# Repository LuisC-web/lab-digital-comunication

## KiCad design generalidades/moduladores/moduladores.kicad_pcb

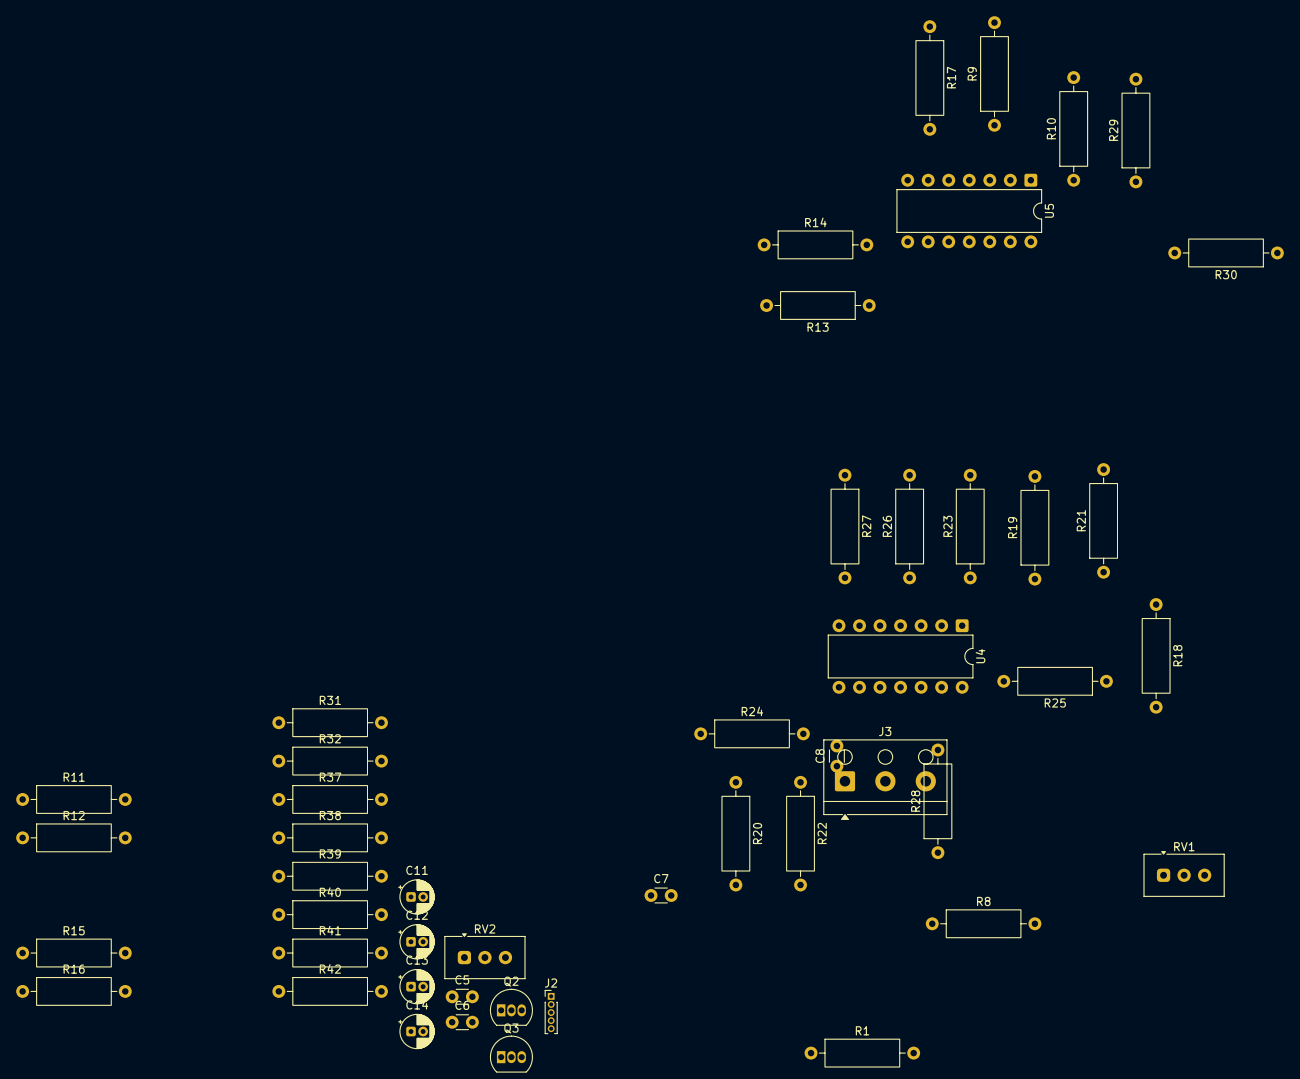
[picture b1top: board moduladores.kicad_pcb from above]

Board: 2 copper layers, 48 parts (0 on the bottom side), 31 nets, no tracks yet.

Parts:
C5, C6, C7, C8: 100nF; C_Disc_D3.0mm_W1.6mm_P2.50mm
C11, C13: 0.1uF; CP_Radial_D4.0mm_P1.50mm
C12, C14: 10uF; CP_Radial_D4.0mm_P1.50mm
J2: Entradas-salidas; PinHeader_1x05_P1.00mm_Vertical
J3: Fuente; TerminalBlock_RND_205-00002_1x03_P5.00mm_Horizontal
Q2, Q3: 2N3904; TO-92_Inline
R1, R8, R18, R19: 10K; R_Axial_DIN0309_L9.0mm_D3.2mm_P12.70mm_Horizontal
R9, R26: 6.8k; R_Axial_DIN0309_L9.0mm_D3.2mm_P12.70mm_Horizontal
R10, R11, R15, R21, R22, R23: 51; R_Axial_DIN0309_L9.0mm_D3.2mm_P12.70mm_Horizontal
R12, R13, R14, R20, R24, R25, R29, R32: 1k; R_Axial_DIN0309_L9.0mm_D3.2mm_P12.70mm_Horizontal
R16, R17, R27, R28: 3.9k; R_Axial_DIN0309_L9.0mm_D3.2mm_P12.70mm_Horizontal
R30, R31: 100k; R_Axial_DIN0309_L9.0mm_D3.2mm_P12.70mm_Horizontal
R37, R38, R39, R40, R41, R42: 220k; R_Axial_DIN0309_L9.0mm_D3.2mm_P12.70mm_Horizontal
RV1, RV2: 50k; Potentiometer_Vishay_T93YA_Vertical
U4, U5: MC1496; DIP-14_W7.62mm

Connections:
+12V: J3.1, Q2.3 (C), Q3.3 (C), R14.1, R16.1, R17.1, R24.1, R27.1, R28.1, R37.1, R40.1
-12V: J3.3, RV1.2, RV2.2, U4.14 (Vee), U5.14 (Vee)
Bcos(wt): C5.1, C12.2
Bsen(wt): C7.1, C14.2
GND: C6.1, C8.1, J3.2, R9.2, R10.2, R11.2, R13.2, R20.2, R21.2, R23.2, R26.2, R29.2, R32.2, R38.2, R39.2, R41.2, R42.2
unnamed: C5.2, R15.2, U5.10
unnamed: C6.2, R13.1, R14.2, R15.1, U5.8
unnamed: C7.2, R22.2, U4.10
unnamed: C8.2, R20.1, R22.1, R24.2, U4.8
unnamed: C13.2, Q2.2 (B), R40.2, R41.1
unnamed: C14.1, Q2.1 (E), R42.1
unnamed: C11.2, Q3.2 (B), R37.2, R38.1
unnamed: C12.1, Q3.1 (E), R39.1
unnamed: R1.2, RV1.3
unnamed: R8.2, RV1.1
unnamed: R9.1, U5.5
unnamed: R8.1, R11.1, U5.4
unnamed: R12.1, U5.2
unnamed: R12.2, U5.3
unnamed: R16.2, U5.12 (Output)
unnamed: R18.2, RV2.3
unnamed: R19.1, R23.1, U4.4
unnamed: R19.2, RV2.1
unnamed: R25.1, U4.2
unnamed: R25.2, U4.3
unnamed: R26.1, U4.5
unnamed: R28.2, U4.12 (Output)
RAI(t): R17.2, U5.6 (Output)
RAQ(t): R27.2, U4.6 (Output)
RI(t): R1.1, R10.1, R29.1, R30.2, U5.1
RQ(t): R18.1, R21.1, R31.2, R32.1, U4.1

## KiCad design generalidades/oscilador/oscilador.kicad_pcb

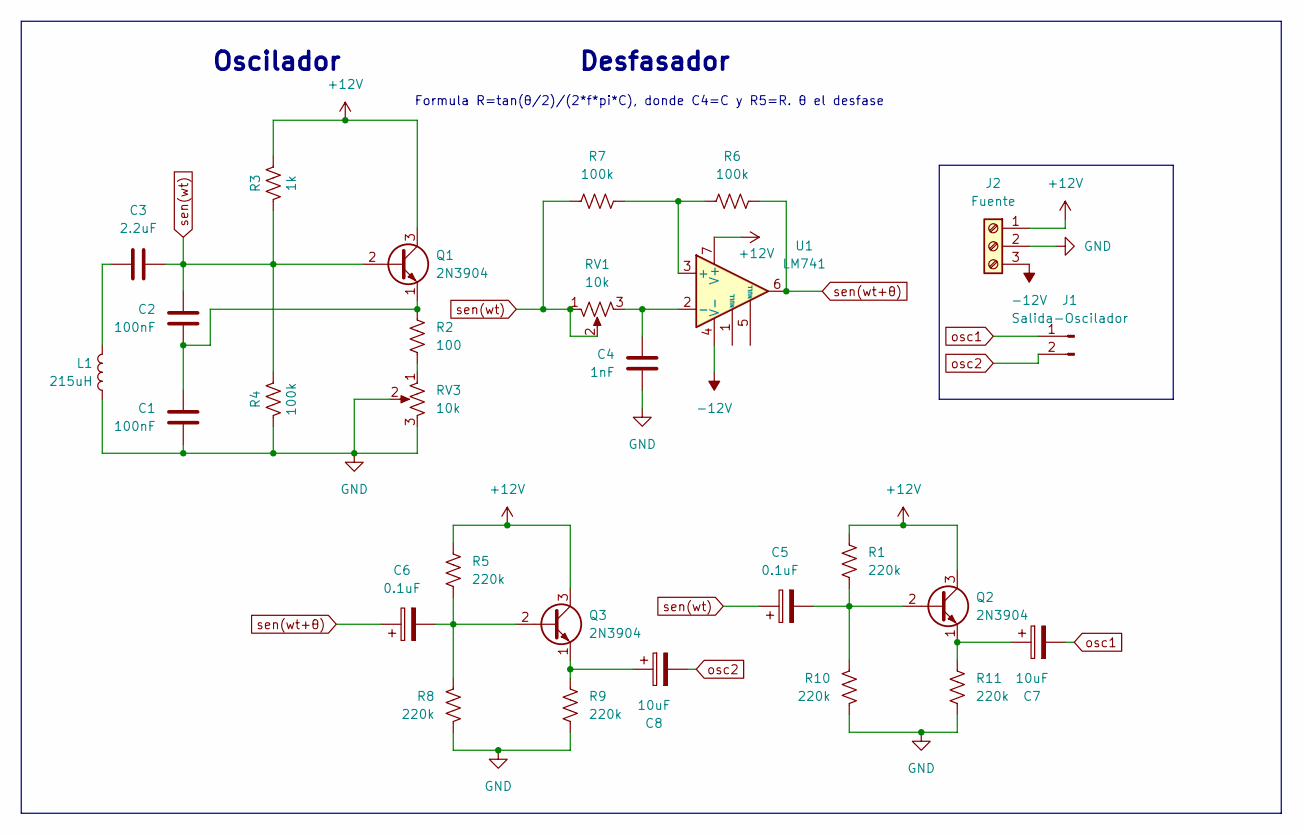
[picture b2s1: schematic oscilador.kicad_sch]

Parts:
C1, C2: 100nF; C_Disc_D3.0mm_W1.6mm_P2.50mm
C3: 2.2uF; C_Disc_D4.3mm_W1.9mm_P5.00mm
C4: 1nF; C_Disc_D3.0mm_W1.6mm_P2.50mm
C5, C6: 0.1uF; CP_Radial_D4.0mm_P1.50mm
C7, C8: 10uF; CP_Radial_D4.0mm_P1.50mm
J1: Salida-Oscilador; PinHeader_1x02_P1.00mm_Vertical
J2: Fuente; TerminalBlock_bornier-3_P5.08mm
L1: 215uH; L_Axial_L7.0mm_D3.3mm_P10.16mm_Horizontal_Fastron_MICC
Q1, Q2, Q3: 2N3904; TO-92_Inline
R1, R5, R8, R9, R10, R11: 220k; R_Axial_DIN0309_L9.0mm_D3.2mm_P12.70mm_Horizontal
R2: 100; R_Axial_DIN0309_L9.0mm_D3.2mm_P12.70mm_Horizontal
R3: 1k; R_Axial_DIN0309_L9.0mm_D3.2mm_P12.70mm_Horizontal
R4, R6, R7: 100k; R_Axial_DIN0309_L9.0mm_D3.2mm_P12.70mm_Horizontal
RV1, RV3: 10k; Potentiometer_Vishay_T93YA_Vertical
U1: LM741; DIP-8_W7.62mm

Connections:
+12V: J2.1, Q1.3 (C), Q2.3 (C), Q3.3 (C), R1.1, R3.1, R5.1, U1.7 (V+)
-12V: J2.3, U1.4 (V-)
GND: C1.2, C4.2, J2.2, L1.2, R4.2, R8.2, R9.2, R10.2, R11.2, RV3.2, RV3.3
unnamed: C3.2, L1.1
unnamed: C1.1, C2.2, Q1.1 (E), R2.1
unnamed: C5.2, Q2.2 (B), R1.2, R10.1
unnamed: C7.1, Q2.1 (E), R11.1
unnamed: C6.2, Q3.2 (B), R5.2, R8.1
unnamed: C8.1, Q3.1 (E), R9.1
unnamed: R2.2, RV3.1
unnamed: R6.1, R7.2, U1.3 (+)
unnamed: C4.1, RV1.3, U1.2 (-)
osc1: C7.2, J1.1
osc2: C8.2, J1.2
sen(wt): C2.1, C3.1, C5.1, Q1.2 (B), R3.2, R4.1, R7.1, RV1.1, RV1.2
sen(wt+θ): C6.1, R6.2, U1.6

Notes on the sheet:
Oscilador
Formula R=tan(θ/2)/(2*f*pi*C), donde C4=C y R5=R. θ el desfase
Desfasador

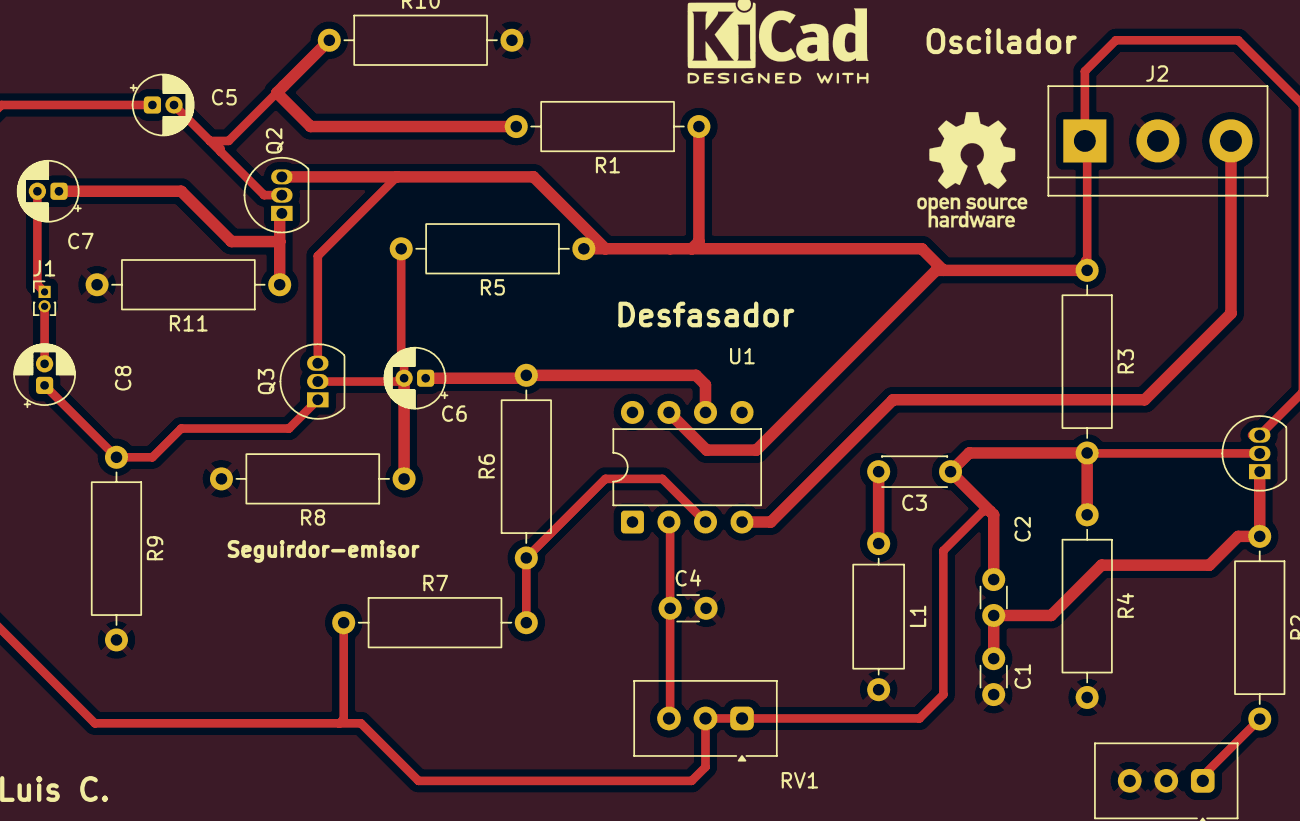
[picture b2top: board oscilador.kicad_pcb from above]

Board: 2 copper layers, 28 parts (0 on the bottom side), 16 nets.

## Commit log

2025-04-06 inicializando repositorio de laboratorios de comunicaciones digitales
2025-04-06 Avanzando en lab 2 decodificador
2025-04-09 Avance del decodificador, falla la muestra final
2025-05-25 Esquemático de laboratorio 3 práctica QAM
2025-05-25 Cambiando los buffer por lm358 e iniciando enrutado
2025-05-25 Cambiando .gitignore por template recomendada https://github.com/github/gitignore/blob/main/KiCad.gitignore
2025-05-25 Cambios en el esquematico, enrutado en pcb y correción de algunos errores
2025-05-25 Fórmulas quiz de digitales
2025-05-28 Separadando por partes. Oscilador y Modulador
2025-06-19 Diseño final de modulador 8QAM
